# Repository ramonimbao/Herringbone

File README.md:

# Herringbone

### Through-hole 75% Keyboard

### Partslist
 |Count|Part|
 |-|-|
 |1|ATmega32A 40 pin DIP|
 |1|40 pin DIP socket|
 |1|HRO-TYPE-C-M-12|
 |1|500 mA polyfuse|
 |2|6mm momentary push buttons|
 |1|16 MHz quartz crystal|
 |1|10 uF electrolytic capacitor|
 |2|100 nF ceramic disk capacitor|
 |2|22 pF ceramic disk capacitor|
 |2|68 Ω resistor|
 |2|1.5 kΩ resistor|
 |2|5.1 kΩ resistor|
 |2|3.6 V zener diode|
 |84|universal switching diode|

This design may be freely produced, modified, and manufactured for **PERSONAL USE ONLY** and may not be reproduced in physical form for public sale.

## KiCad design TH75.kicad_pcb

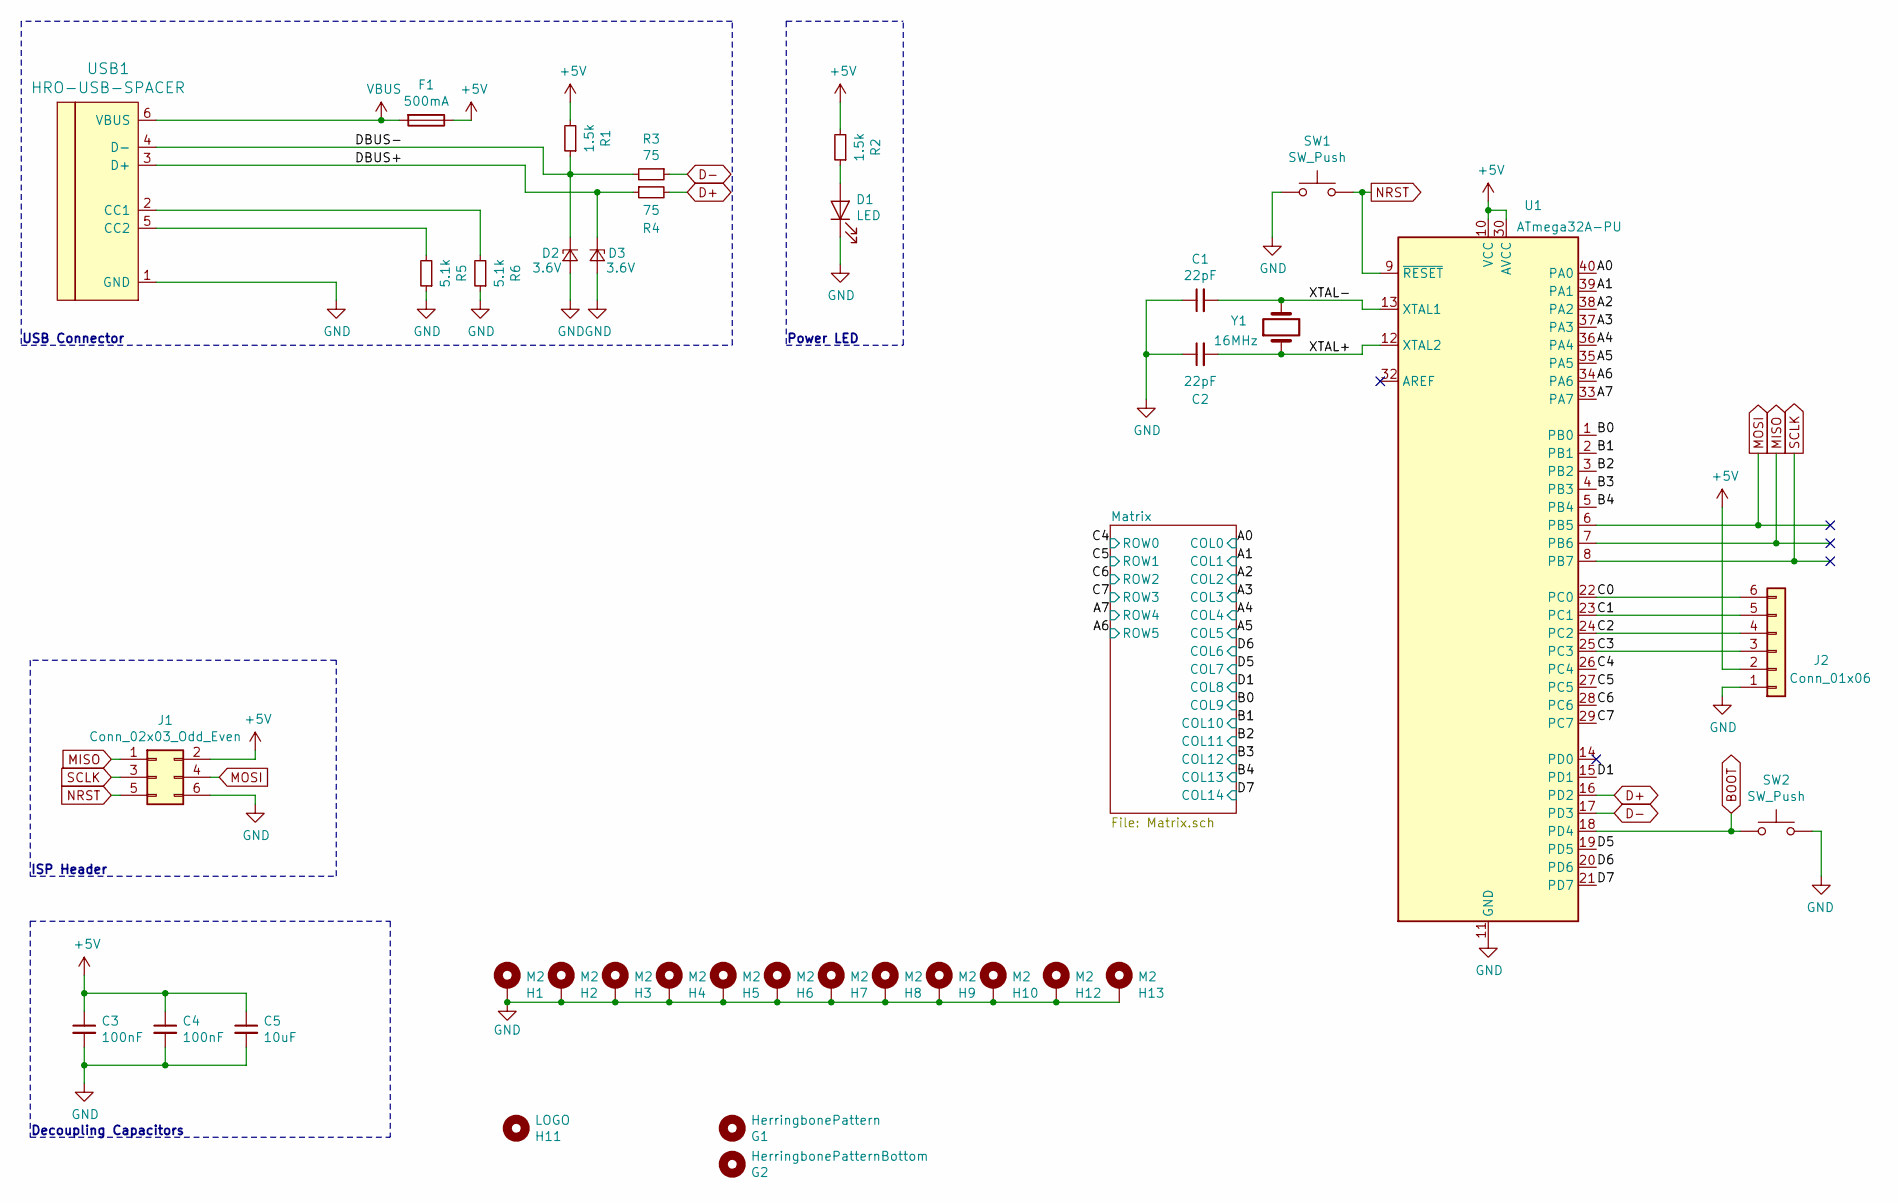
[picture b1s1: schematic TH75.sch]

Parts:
C1, C2: 22pF; C_Disc_D3.0mm_W1.6mm_P2.50mm
C3, C4: 100nF; C_Disc_D4.3mm_W1.9mm_P5.00mm
C5: 10uF; CP_Radial_D4.0mm_P1.50mm
D1: LED; LED_D3.0mm
D2, D3: 3.6V; D_DO-34_SOD68_P7.62mm_Horizontal
F1: 500mA; C_Disc_D5.0mm_W2.5mm_P5.00mm
G1: HerringbonePattern; front-pattern
G2: HerringbonePatternBottom; main-bottom-pattern
H1, H2, H3, H4, H5, H6, H7, H8, H9, H10, H12, H13: M2; MountingHole_2.2mm_M2_Pad_Via
H11: LOGO; Signature
J1: Conn_02x03_Odd_Even; Reset_Pretty
J2: Conn_01x06; PinSocket_1x06_P2.54mm_Vertical
R1, R2: 1.5k; R_Axial_DIN0204_L3.6mm_D1.6mm_P5.08mm_Horizontal
R3, R4: 75; R_Axial_DIN0204_L3.6mm_D1.6mm_P5.08mm_Horizontal
R5, R6: 5.1k; R_Axial_DIN0204_L3.6mm_D1.6mm_P5.08mm_Horizontal
SW1, SW2: SW_Push; SW_PUSH_6mm
U1: ATmega32A-PU; DIP-40_W15.24mm_Socket
USB1: HRO-USB-SPACER; HRO-TYPE-C-31-M-12-USB-Spacer
Y1: 16MHz; Crystal_HC49-4H_Vertical

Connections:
+5V: C3.1, C4.1, C5.1, F1.1, J1.2, J2.2, R1.2, R2.2, U1.10 (VCC), U1.30 (AVCC)
/A0: U1.40 (PA0); also elsewhere on the board
/A1: U1.39 (PA1); also elsewhere on the board
/A2: U1.38 (PA2); also elsewhere on the board
/A3: U1.37 (PA3); also elsewhere on the board
/A4: U1.36 (PA4); also elsewhere on the board
/A5: U1.35 (PA5); also elsewhere on the board
/A6: U1.34 (PA6); also elsewhere on the board
/A7: U1.33 (PA7); also elsewhere on the board
/B0: U1.1 (PB0); also elsewhere on the board
/B1: U1.2 (PB1); also elsewhere on the board
/B2: U1.3 (PB2); also elsewhere on the board
/B3: U1.4 (PB3); also elsewhere on the board
/B4: U1.5 (PB4); also elsewhere on the board
/C0: J2.6, U1.22 (PC0)
/C1: J2.5, U1.23 (PC1)
/C2: J2.4, U1.24 (PC2)
/C3: J2.3, U1.25 (PC3)
/C4: U1.26 (PC4); also elsewhere on the board
/C5: U1.27 (PC5); also elsewhere on the board
/C6: U1.28 (PC6); also elsewhere on the board
/C7: U1.29 (PC7); also elsewhere on the board
/D1: U1.15 (PD1); also elsewhere on the board
/D5: U1.19 (PD5); also elsewhere on the board
/D6: U1.20 (PD6); also elsewhere on the board
/D7: U1.21 (PD7); also elsewhere on the board
/DBUS+: D3.1 (K), R4.1, USB1.3 (D+)
/DBUS-: D2.1 (K), R1.1, R3.2, USB1.4 (D-)
/XTAL+: C2.2, U1.12 (XTAL2), Y1.1
/XTAL-: C1.2, U1.13 (XTAL1), Y1.2
BOOT: SW2.2, U1.18 (PD4)
D+: R4.2, U1.16 (PD2)
D-: R3.1, U1.17 (PD3)
GND: C1.1, C2.1, C3.2, C4.2, C5.2, D1.1 (K), D2.2 (A), D3.2 (A), H1.1, H2.1, H3.1, H4.1, H5.1, H6.1, H7.1, H8.1, H9.1, H10.1, H12.1, H13.1, J1.6, J2.1, R5.1, R6.1, SW1.1, SW2.1, U1.11 (GND), U1.31 (GND), USB1.1 (GND)
MISO: J1.1, U1.7 (PB6)
MOSI: J1.4, U1.6 (PB5)
NRST: J1.5, SW1.2, U1.9 (~RESET)
unnamed: D1.2 (A), R2.1
unnamed: R5.2, USB1.5 (CC2)
unnamed: R6.2, USB1.2 (CC1)
SCLK: J1.3, U1.8 (PB7)
VBUS: F1.2, USB1.6 (VBUS)

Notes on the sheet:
USB Connector
ISP Header
Decoupling Capacitors
Power LED

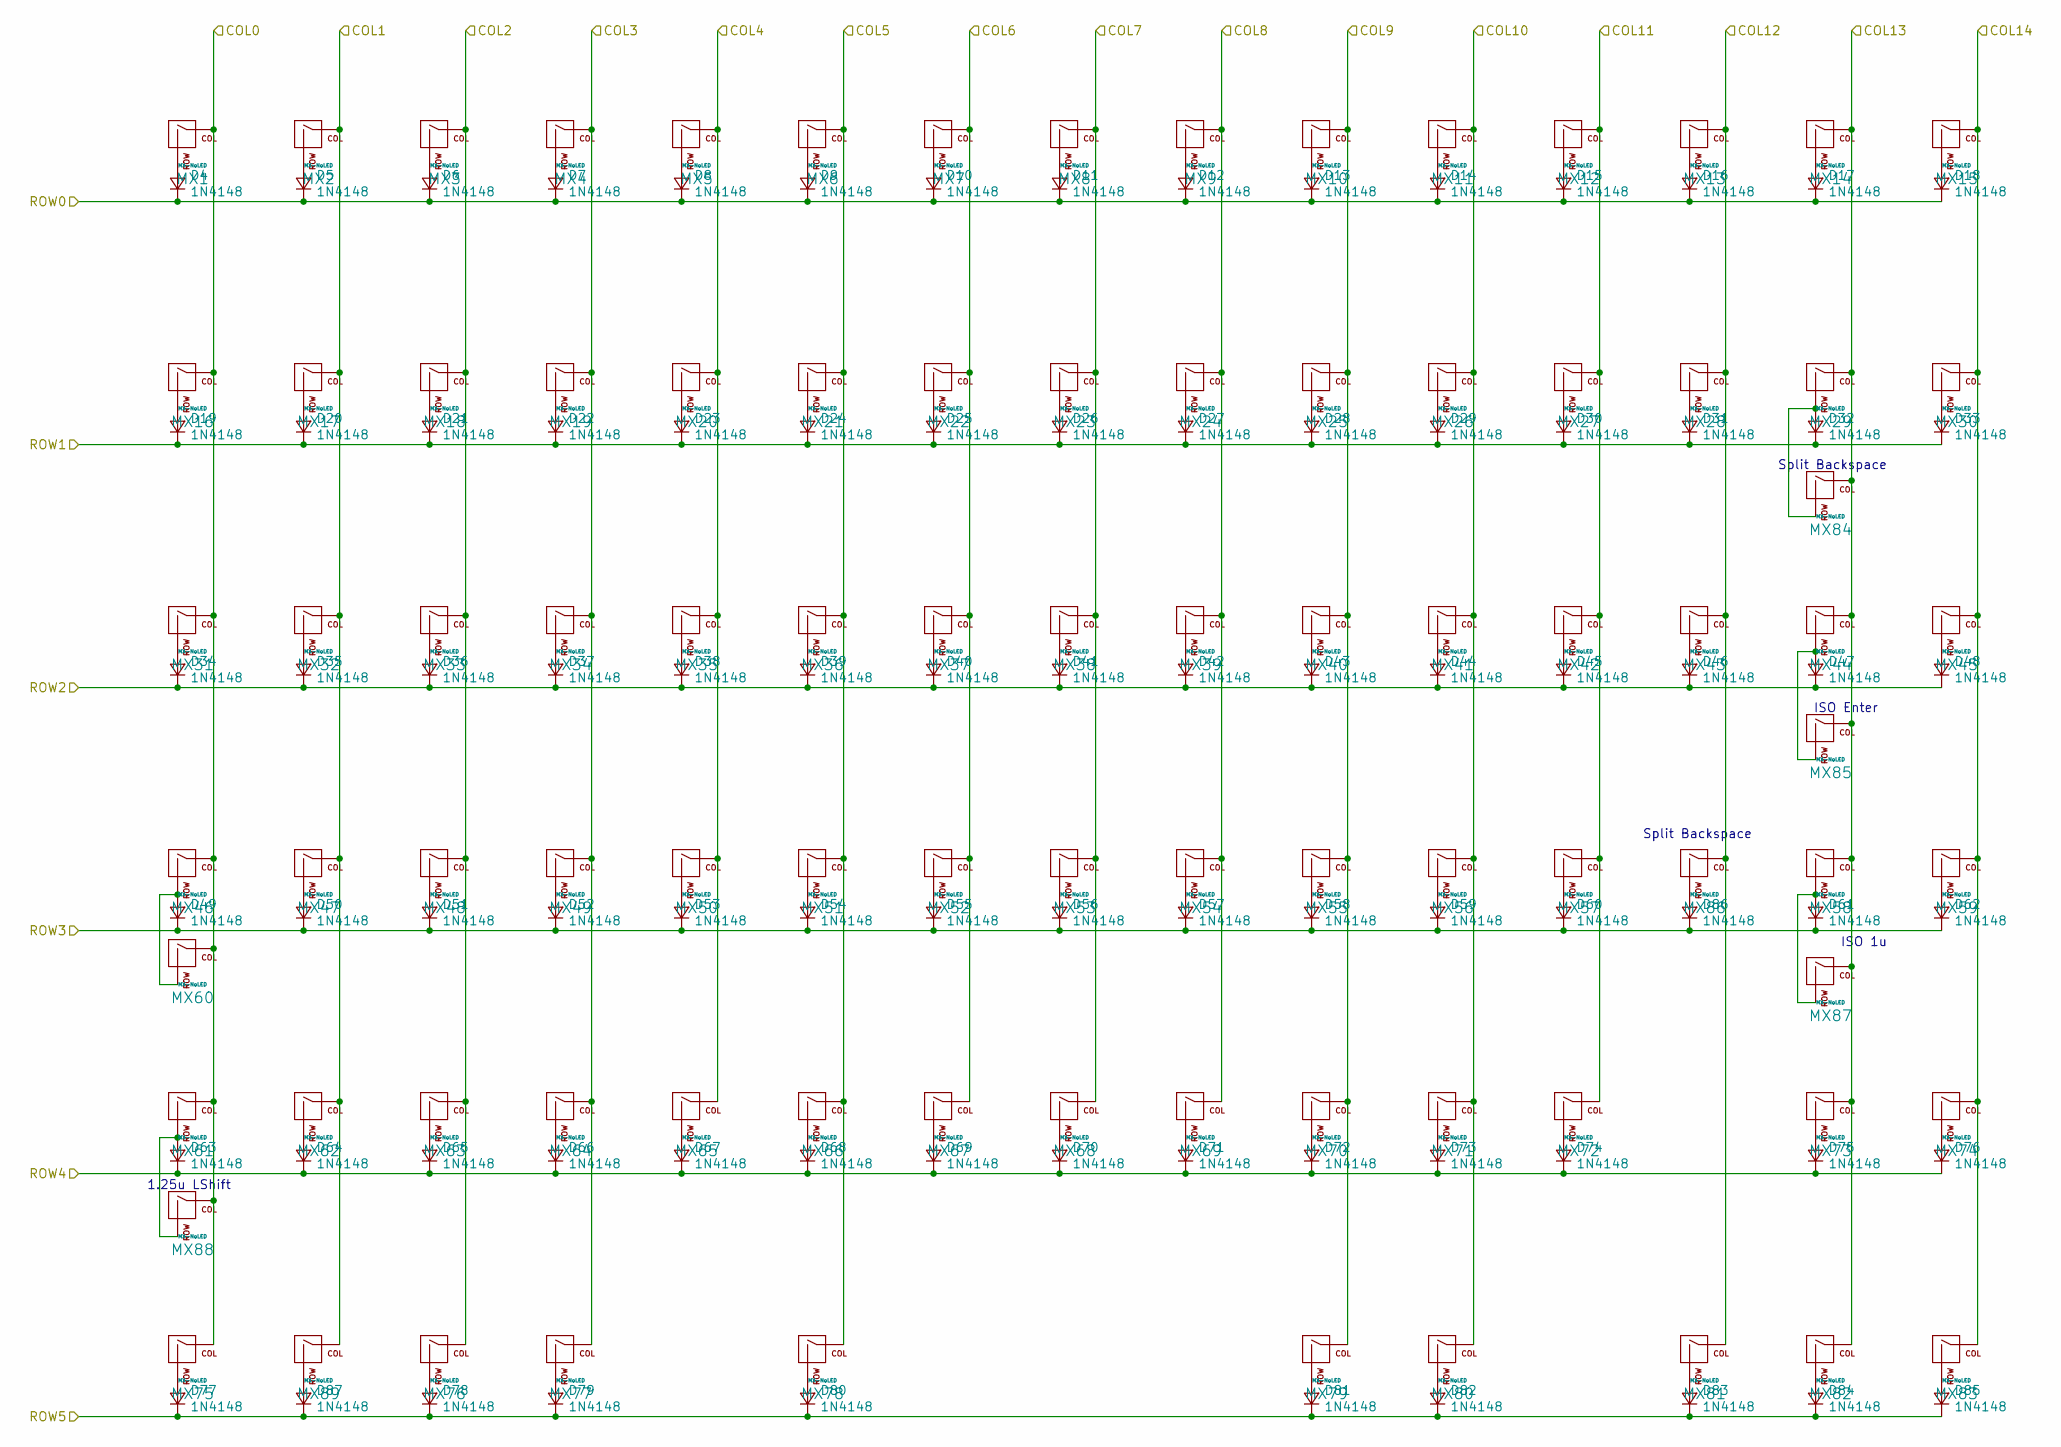
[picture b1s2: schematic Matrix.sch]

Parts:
D4, D5, D6, D7, D8, D9, D10, D11, D12, D13, D14, D15, D16, D17, D18, D19, D20, D21, D22, D23, D24, D25, D26, D27, D28, D29, D30, D31, D32, D33, D34, D35, D36, D37, D38, D39, D40, D41, D42, D43, D44, D45, D46, D47, D48, D49, D50, D51, D52, D53, D54, D55, D56, D57, D58, D59, D60, D61, D62, D63, D64, D65, D66, D67, D68, D69, D70, D71, D72, D73, D74, D75, D76, D77, D78, D79, D80, D81, D82, D83, D84, D85, D86, D87: 1N4148; D_DO-34_SOD68_P7.62mm_Horizontal
MX1, MX2, MX3, MX4, MX5, MX6, MX7, MX8, MX9, MX10, MX11, MX12, MX13, MX14, MX15, MX16, MX17, MX18, MX19, MX20, MX21, MX22, MX23, MX24, MX25, MX26, MX27, MX28, MX30, MX32, MX33, MX34, MX35, MX36, MX37, MX38, MX39, MX40, MX41, MX42, MX43, MX45, MX47, MX48, MX49, MX50, MX51, MX52, MX53, MX54, MX55, MX56, MX57, MX59, MX62, MX63, MX64, MX65, MX66, MX67, MX68, MX69, MX70, MX71, MX73, MX74, MX81, MX82, MX83, MX84, MX86, MX87, MX89: MX-NoLED; MXOnly-1U-NoLED
MX29: MX-NoLED; MXOnly-2U-NoLED
MX31, MX44, MX79, MX80: MX-NoLED; MXOnly-1.5U-NoLED
MX46, MX72: MX-NoLED; MXOnly-1.75U-NoLED
MX58, MX61: MX-NoLED; MXOnly-2.25U-NoLED
MX60, MX75, MX76, MX77, MX88: MX-NoLED; MXOnly-1.25U-NoLED
MX78: MX-NoLED; MXOnly-6.25U-ReversedStabilizers-NoLED
MX85: MX-NoLED; MXOnly-ISO-ROTATED-ReversedStabilizers-NoLED

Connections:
/A0: MX1.1 (COL), MX16.1 (COL), MX31.1 (COL), MX46.1 (COL), MX60.1 (COL), MX61.1 (COL), MX75.1 (COL), MX88.1 (COL); also elsewhere on the board
/A1: MX2.1 (COL), MX17.1 (COL), MX32.1 (COL), MX47.1 (COL), MX62.1 (COL), MX89.1 (COL); also elsewhere on the board
/A2: MX3.1 (COL), MX18.1 (COL), MX33.1 (COL), MX48.1 (COL), MX63.1 (COL), MX76.1 (COL); also elsewhere on the board
/A3: MX4.1 (COL), MX19.1 (COL), MX34.1 (COL), MX49.1 (COL), MX64.1 (COL), MX77.1 (COL); also elsewhere on the board
/A4: MX5.1 (COL), MX20.1 (COL), MX35.1 (COL), MX50.1 (COL), MX65.1 (COL); also elsewhere on the board
/A5: MX6.1 (COL), MX21.1 (COL), MX36.1 (COL), MX51.1 (COL), MX66.1 (COL), MX78.1 (COL); also elsewhere on the board
/A6: D77.1 (K), D78.1 (K), D79.1 (K), D80.1 (K), D81.1 (K), D82.1 (K), D83.1 (K), D84.1 (K), D85.1 (K), D87.1 (K); also elsewhere on the board
/A7: D63.1 (K), D64.1 (K), D65.1 (K), D66.1 (K), D67.1 (K), D68.1 (K), D69.1 (K), D70.1 (K), D71.1 (K), D72.1 (K), D73.1 (K), D74.1 (K), D75.1 (K), D76.1 (K); also elsewhere on the board
/B0: MX10.1 (COL), MX25.1 (COL), MX40.1 (COL), MX55.1 (COL), MX70.1 (COL), MX79.1 (COL); also elsewhere on the board
/B1: MX11.1 (COL), MX26.1 (COL), MX41.1 (COL), MX56.1 (COL), MX71.1 (COL), MX80.1 (COL); also elsewhere on the board
/B2: MX12.1 (COL), MX27.1 (COL), MX42.1 (COL), MX57.1 (COL), MX72.1 (COL); also elsewhere on the board
/B3: MX13.1 (COL), MX28.1 (COL), MX43.1 (COL), MX81.1 (COL), MX86.1 (COL); also elsewhere on the board
/B4: MX14.1 (COL), MX29.1 (COL), MX44.1 (COL), MX58.1 (COL), MX73.1 (COL), MX82.1 (COL), MX84.1 (COL), MX85.1 (COL), MX87.1 (COL); also elsewhere on the board
/C4: D4.1 (K), D5.1 (K), D6.1 (K), D7.1 (K), D8.1 (K), D9.1 (K), D10.1 (K), D11.1 (K), D12.1 (K), D13.1 (K), D14.1 (K), D15.1 (K), D16.1 (K), D17.1 (K), D18.1 (K); also elsewhere on the board
/C5: D19.1 (K), D20.1 (K), D21.1 (K), D22.1 (K), D23.1 (K), D24.1 (K), D25.1 (K), D26.1 (K), D27.1 (K), D28.1 (K), D29.1 (K), D30.1 (K), D31.1 (K), D32.1 (K), D33.1 (K); also elsewhere on the board
/C6: D34.1 (K), D35.1 (K), D36.1 (K), D37.1 (K), D38.1 (K), D39.1 (K), D40.1 (K), D41.1 (K), D42.1 (K), D43.1 (K), D44.1 (K), D45.1 (K), D46.1 (K), D47.1 (K), D48.1 (K); also elsewhere on the board
/C7: D49.1 (K), D50.1 (K), D51.1 (K), D52.1 (K), D53.1 (K), D54.1 (K), D55.1 (K), D56.1 (K), D57.1 (K), D58.1 (K), D59.1 (K), D60.1 (K), D61.1 (K), D62.1 (K), D86.1 (K); also elsewhere on the board
/D1: MX9.1 (COL), MX24.1 (COL), MX39.1 (COL), MX54.1 (COL), MX69.1 (COL); also elsewhere on the board
/D5: MX8.1 (COL), MX23.1 (COL), MX38.1 (COL), MX53.1 (COL), MX68.1 (COL); also elsewhere on the board
/D6: MX7.1 (COL), MX22.1 (COL), MX37.1 (COL), MX52.1 (COL), MX67.1 (COL); also elsewhere on the board
/D7: MX15.1 (COL), MX30.1 (COL), MX45.1 (COL), MX59.1 (COL), MX74.1 (COL), MX83.1 (COL); also elsewhere on the board
unnamed: D4.2 (A), MX1.2 (ROW)
unnamed: D5.2 (A), MX2.2 (ROW)
unnamed: D6.2 (A), MX3.2 (ROW)
unnamed: D7.2 (A), MX4.2 (ROW)
unnamed: D8.2 (A), MX5.2 (ROW)
unnamed: D9.2 (A), MX6.2 (ROW)
unnamed: D10.2 (A), MX7.2 (ROW)
unnamed: D11.2 (A), MX8.2 (ROW)
unnamed: D12.2 (A), MX9.2 (ROW)
unnamed: D13.2 (A), MX10.2 (ROW)
unnamed: D14.2 (A), MX11.2 (ROW)
unnamed: D15.2 (A), MX12.2 (ROW)
unnamed: D16.2 (A), MX13.2 (ROW)
unnamed: D17.2 (A), MX14.2 (ROW)
unnamed: D18.2 (A), MX15.2 (ROW)
unnamed: D19.2 (A), MX16.2 (ROW)
unnamed: D20.2 (A), MX17.2 (ROW)
unnamed: D21.2 (A), MX18.2 (ROW)
unnamed: D22.2 (A), MX19.2 (ROW)
unnamed: D23.2 (A), MX20.2 (ROW)
unnamed: D24.2 (A), MX21.2 (ROW)
unnamed: D25.2 (A), MX22.2 (ROW)
unnamed: D26.2 (A), MX23.2 (ROW)
unnamed: D27.2 (A), MX24.2 (ROW)
unnamed: D28.2 (A), MX25.2 (ROW)
unnamed: D29.2 (A), MX26.2 (ROW)
unnamed: D30.2 (A), MX27.2 (ROW)
unnamed: D31.2 (A), MX28.2 (ROW)
unnamed: D32.2 (A), MX29.2 (ROW), MX84.2 (ROW)
unnamed: D33.2 (A), MX30.2 (ROW)
unnamed: D34.2 (A), MX31.2 (ROW)
unnamed: D35.2 (A), MX32.2 (ROW)
unnamed: D36.2 (A), MX33.2 (ROW)
unnamed: D37.2 (A), MX34.2 (ROW)
unnamed: D38.2 (A), MX35.2 (ROW)
unnamed: D39.2 (A), MX36.2 (ROW)
unnamed: D40.2 (A), MX37.2 (ROW)
unnamed: D41.2 (A), MX38.2 (ROW)
unnamed: D42.2 (A), MX39.2 (ROW)
unnamed: D43.2 (A), MX40.2 (ROW)
unnamed: D44.2 (A), MX41.2 (ROW)
unnamed: D45.2 (A), MX42.2 (ROW)
unnamed: D46.2 (A), MX43.2 (ROW)
unnamed: D47.2 (A), MX44.2 (ROW), MX85.2 (ROW)
unnamed: D48.2 (A), MX45.2 (ROW)
unnamed: D49.2 (A), MX46.2 (ROW), MX60.2 (ROW)
unnamed: D50.2 (A), MX47.2 (ROW)
unnamed: D51.2 (A), MX48.2 (ROW)
unnamed: D52.2 (A), MX49.2 (ROW)
unnamed: D53.2 (A), MX50.2 (ROW)
unnamed: D54.2 (A), MX51.2 (ROW)
unnamed: D55.2 (A), MX52.2 (ROW)
unnamed: D56.2 (A), MX53.2 (ROW)
unnamed: D57.2 (A), MX54.2 (ROW)
unnamed: D58.2 (A), MX55.2 (ROW)
unnamed: D59.2 (A), MX56.2 (ROW)
unnamed: D60.2 (A), MX57.2 (ROW)
unnamed: D61.2 (A), MX58.2 (ROW), MX87.2 (ROW)
unnamed: D62.2 (A), MX59.2 (ROW)
unnamed: D63.2 (A), MX61.2 (ROW), MX88.2 (ROW)
unnamed: D64.2 (A), MX62.2 (ROW)
unnamed: D65.2 (A), MX63.2 (ROW)
unnamed: D66.2 (A), MX64.2 (ROW)
unnamed: D67.2 (A), MX65.2 (ROW)
unnamed: D68.2 (A), MX66.2 (ROW)
unnamed: D69.2 (A), MX67.2 (ROW)
unnamed: D70.2 (A), MX68.2 (ROW)
unnamed: D71.2 (A), MX69.2 (ROW)
unnamed: D72.2 (A), MX70.2 (ROW)
unnamed: D73.2 (A), MX71.2 (ROW)
unnamed: D74.2 (A), MX72.2 (ROW)
unnamed: D75.2 (A), MX73.2 (ROW)
unnamed: D76.2 (A), MX74.2 (ROW)
unnamed: D77.2 (A), MX75.2 (ROW)
unnamed: D78.2 (A), MX76.2 (ROW)
unnamed: D79.2 (A), MX77.2 (ROW)
unnamed: D80.2 (A), MX78.2 (ROW)
unnamed: D81.2 (A), MX79.2 (ROW)
unnamed: D82.2 (A), MX80.2 (ROW)
unnamed: D83.2 (A), MX81.2 (ROW)
unnamed: D84.2 (A), MX82.2 (ROW)
unnamed: D85.2 (A), MX83.2 (ROW)
unnamed: D86.2 (A), MX86.2 (ROW)
unnamed: D87.2 (A), MX89.2 (ROW)

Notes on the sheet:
1.25u LShift
Split Backspace
ISO Enter
ISO 1u

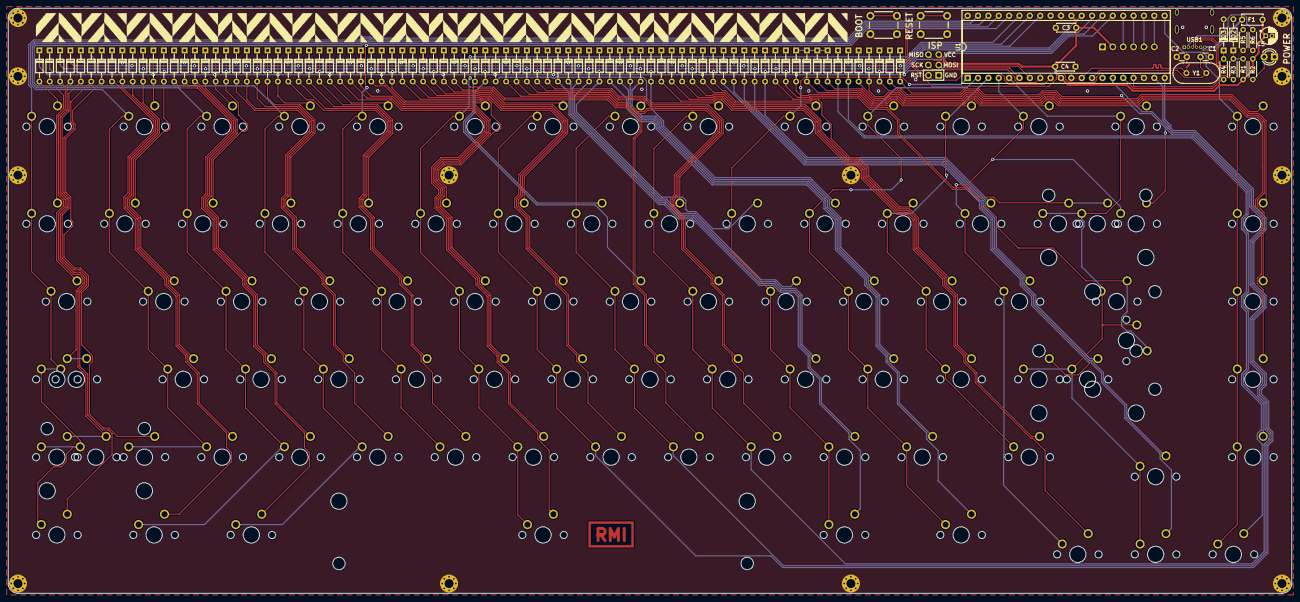
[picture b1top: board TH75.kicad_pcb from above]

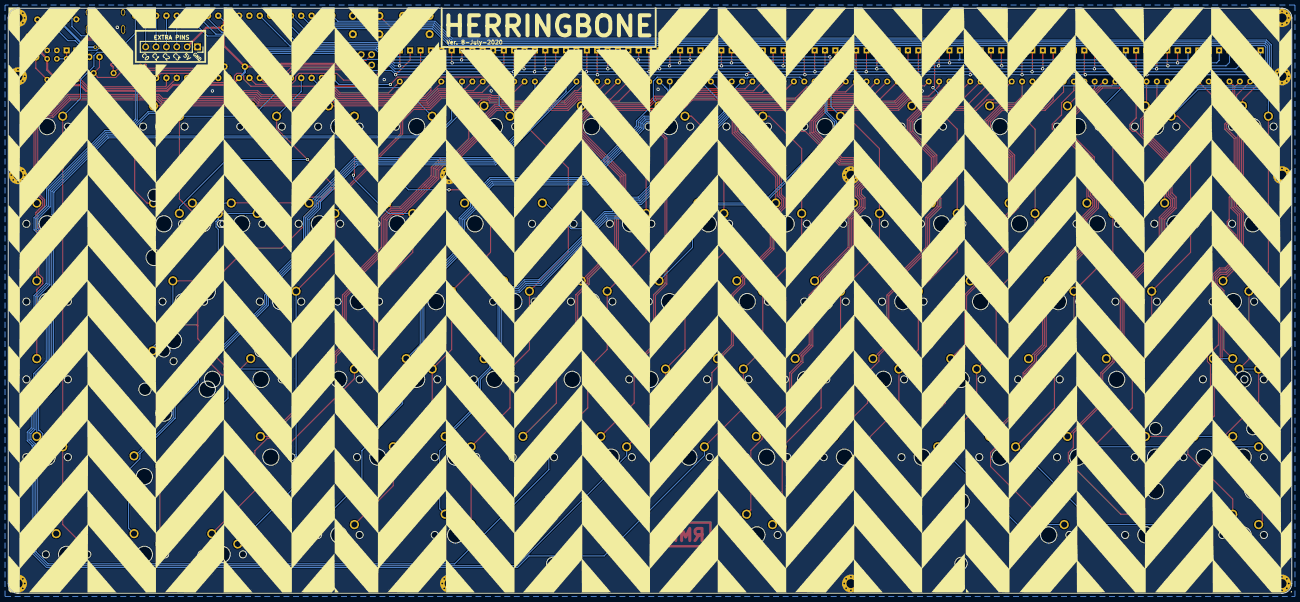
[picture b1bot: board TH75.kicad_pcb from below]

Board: 2 copper layers, 314.3 x 143.3 mm, 210 parts (2 on the bottom side), 126 nets.

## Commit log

2020-11-28 Readd LICENSE
